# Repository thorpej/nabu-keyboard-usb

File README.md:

# A NABU Keyboard-to-USB Adapter

(Update: I made a short video about this project!  You can view it
[here](https://youtu.be/F3Tp9NLZv1M).)

This is an adapter that lets you connect a [NABU](https://nabu.ca/) PC
keyboard to any modern computer using USB.  In addition to the keyboard,
it reports the Atari-style joysticks as USB HID gamepads (each as a single
D-pad / hat switch with a single "A" button).

Most of the NABU keys are supported in the obvious way, but it's helpful
to understand how the NABU keyboard works: The keyboard, for the most part,
sends ASCII codes for the keys that are pressed.  It handles CTRL, SHIFT,
and CAPS-LOCK all on its own.  It does not send separate key-down and key-up
events for the standard keys, and it implements key-repeat itself as well.
There are some exceptions, however: the arrow keys (including the **<|||**
and **|||>** keys), **YES**, **NO**, **SYM**, **PAUSE** and **TV/NABU** keys
_do_ send separate key-down and key-up events, and are unaffected by the
normal keyboard modifier keys.  These so-called "special keys" are mapped
to various HID key events as described below.

The physical interface to the NABU keyboard is a DIN-6 connector carrying
a power rail and an RS422 differential transmit line.  The RS422 serial
line runs at 6992 baud, with 8 data bits, 1 stop bit, and no parity.  The
odd-ball bit rate is due to the way the clock is derived; the main clock
frequency in the keyboard is 3.58MHz (the NTSC colorburst frequency), and
the MC6803 microcontroller inside the keyboard internally divides the clock
by 4 to derive its "E" clock.  The firmware in the keyboard then configures
the MC6803's on-board UART to divide E by 128 for the baud clock.
Communication with the keyboard is unidirectional; it is not possible to
send commands to the keyboard.

The keyboard is powered by a nominally-12V-but-actally-9V power supply
provided by the NABU.  The keyboard power comes from the NABU's 12V rail,
but is fed to the keyboard through a large power resistor on the NABU's
mainboard, which drops the voltage to ~9V at the keyboard's steady-state
current draw (documentation says 300mA, but my bench supply tells me
310-320mA).  The keyboard contains an on-board regulator to provide its
own +5V power rail.  In any case, a 9V DC power brick that can supply at
least 500mA should be perfect for the job.  The adapter controls the power
to the NABU using a small power MOSFET connected between the 9V return from
the keyboard and and negative terminal of the power supply.

## How the adapter works

The adapter utilizes the built-in UART and GPIO functionality of the
Raspberry Pi Pico microcontroller.  UART0 is used as the adapter's console
(115200 @ 8N1), UART1 is used to receive data from the keyboard, and one
GPIO pin is used to control the power to the keyboard.  Another GPIO is
sampled at start-up time to enable debug messages; debugging is enabled
when the jumper is installed.

When the adapter starts up, it performs all of the initialization required
and then starts up the second core on the Pico to pull data in from the
keyboard.  This loop running on the second core determines if the data is
for the keyboard or one of the joysticks, and then adds the data byte to
the appropriate input queue.

Meanwhile, the primary core powers up the keyboard and enters its main loop.
This main loop performs 4 basic tasks:
* Blinking the status LED on the Pico to indicate various states of the
  adapter.
* Performing a health check of the keyboard.
* Processing incoming data from the keyboard and generating the appropriate
  USB HID report sequences.
* Calling into the TinyUSB stack to perform device-side USB processing.

### LED task

The LED task is pretty simple and just provides a simple way of reporting
the current status of the adapter at-a-glance.  There are 4 blinking sequences:
* Fast blinking to indicate the adapter is waiting for the host to establish
  a USB session.
* Medium blinking to indicate the adapter is connected to the host but waiting
  for the keyboard to show signs of life.
* A heatbeat pattern to indicate everything is operating normally.
* A slow blinking to indicate the adapter has been suspended and the keyboard
  powered off.

### Keyboard health check task

The health check task (a.k.a. "deadcheck") checks to make sure that we've
heard from the keyboard within the last 5 seconds.  When idle, the keyboard
sends a "ping" approximately every 3.7 seconds.  Whenever the keyboard reader
running on the second core receives a byte of data from the keyboard, it
updates a timestamp, which is checked in deadcheck routine.  If the keyboard
fails to check in for two deadcheck intervals, the adapter reboots the
keyboard by cycling power.

### Data processing task

The data processing task (called _hid_task()_ in the code) pulls data
enqueued by the keyboard reader thread and performs the processing necessary
to generate USB HID report sequences.  In addition to regular keystrokes,
error messages from the keyboard and joystick data are also processed here,
as is remote-host-wakeup if the host system is suspended.

Error processing is actually performed all the time, because the periodic
ping from the keyboard comes in as an error message, as does the notification
of a successful power-on-reset.  Additionally, there are internal hardware
errors (bad RAM / ROM, etc.) as well as user errors (too many keys pressed)
that are reported.  Hardware errors result in rebooting the keyboard by
cycling power.

Because the NABU keyboard generates only a single byte for most key presses,
this task has to generate HID report sequences to correctly report the key.
For example, if we get "A" from the keyboard, we have to generate a sequence
of 4 HID reports: _SHIFT_, _SHIFT_ + _A_, _SHIFT_, _(none)_.  These sequences
are encoded in a table indexed by NABU keyboard code.  All of the regular
keys end with a _(none)_ report.

The special keys are a little different.  They send individual key-down and
key-up events to the adapter, so we are able to simply mirror that behavior
to the host.  Additionally, two of the special keys have been mapped to key
modifiers: **SYM** is mapped to **Meta** (a.k.a. Windows, Command, or GUI).
and the **TV/NABU** key is mapped to **Alt** (a.k.a. Option on Macs).  The
adapter tracks the state of those keys and includes them as modifiers in
keyboard HID reports.

Much to the chargin of Unix users worldwide, the NABU keyboard lacks a
backslash key.  On US keyboards, this key is also used for the "pipe"
character (SHIFT + backslash).  We steal the **YES** and **NO** keys on
the NABU keyboard for these characters: **YES** for pipe, **NO** for
backslash (we have to use two different special keys since special keys
are not affected by the SHIFT keys).  Luckily, because we're using a
special key for **Alt**, we can still type guillemets on a Mac by using
**TV/NABU** plus the **YES** and **NO** keys.  _«Absolument merveilleux !»,
a-t-il déclaré._

Ok! To summarize the special keys:
* **Up**, **Down**, **Left**, and **Right** arrow keys map to their regular
  US keyboard equivalents.
* **<|||** maps to **Page Up** and **|||>** maps to **Page Down** (very
  useful for scrolling in Terminal on macOS).
* **SYM** maps to **Meta**, a.k.a. **Windows**, **Command**, **GUI**,
  **⌘**, etc.
* **TV/NABU** maps to **Alt**, a.k.a. **Option**, **⌥**, etc.
* **NO** maps to **\\**, a.k.a. backslash.
* **YES** maps to **|**, a.k.a. pipe, vertical bar, etc. 

### TinyUSB device task

This is just a call into the TinyUSB library that performs device-side
processing.  From here, various callbacks back into the main adapter code
can be made to fetch descriptors, reports, and set suspend/resume state.

## The hardware

The hardware is very simple and is centered around the Raspberry Pi Pico
microcontroller board, wich provides a UART for the debug console, a UART
for the keyboard interface, the USB interface to the host, and general-
purpose I/O facilities for configuration of the adapter and control of the
keyboard's power supply.

Note that the adapter board has 3 separate power rails: +5V (supplied by
the USB host), +3V3 (from the Pico's on-board regulator), and +9V (from an
external DC power brick, for the keyboard).

### Keyboard input

The keyboard uses RS422 differential signalling, so a SN75176A differential
bus transciever is used to convert the keyboard signalling to a TTL-compatible
signal.  The transient suppression circuitry mimics that present in the NABU
PC.

The output of the SN75176A is at 5V TTL logic levels, but the Pico's I/O
interface operates at 3V3 CMOS logic levels, so a level shifter must be
used.  I just picked the 74LVC245 bus transciever for the job because I
had plenty of them handy, even though it's slight overkill.

The 74LVC245's output is connected to the Rx pin of UART1 on the Pico.
That's pretty much it for the keyboard input.

### Keyboard power supply / control

The board has a 5.5mm x 2.1mm center-positive barrel jack for power input
from an external 9V power brick.  There is a diode in-series with the
positive terminal as reverse-polarity protection.  The positive terminal
from this supply goes stright to the keyboard.  The power return line
from the keyboard is attached to the drain of an IRLU110PBF power MOSFET,
and the MOSFET's source is then connected to the negative terminal of the
supply, which is also connected to the board's ground plane.  The gate is
normally pulled down, but can be driven high by a pin on the Pico to complete
the circuit and power on the keyboard.  The IRLU110PBF was selected for its
current rating, relatively low as far as power MOSFETs go (1V) Vgs threshold,
and < 1 Ohm Rds-ON.  There's nothing particularly special about it otherwise,
and this application isn't especially demanding, so feel free to substitute
your favorite MOSFET (so long as it is in a TO-251-3 package and has a GDS
pin configuration).

### Pin headers

There are 2 pin headers on the board:
* J1 provides access to UART0 on the Pico, so you can see informational or
  debug messages that are logged by the firmware running on the Pico.
* JP1, when connected, enables those fairly verbose debugging messages.  The
  pin is sampled when the adapter starts up, so enabling them requires
  unplugging the adapter from USB and plugging it back in after connecting
  the jumper.

### The board layout

I am definitely an amateur when it comes to PCB design and layout, but I did
try to keep the board fairly small while still making it easy to assemble
(all through-hole parts except for the tab on the power MOSFET which you don't
even _really_ have to solder if that's your preference).  The footprints for
the decoupling caps and suppression caps are fairly forgiving, so if you have
1nF and 100nF caps in your parts bin that fit the footprint, by all means use
them.

You will need to put downward-facing pin headers onto your Pico and install
female pin header stand-offs onto the board.  This is because I squeezed the
power MOSFET and its pulldown resistor under the Pico.  This isn't really
much of a compromise in height since there's a big ol' DIN-6 socket at the
back of the board anyhow.  (The board size is largely dictated by the external
connections.)

Space for sockets for the DIP ICs is provided because I like to use them.
Feel free to elide if that's what floats your boat.

There are a couple of "special" parts on the board:
* The resistors used on the board are fairly small for through-hole resistors,
  selected to reduce space requirements.  Happily, they're readily available
  from Mouser.
* The DIN-6 socket is harder to get than it should be (plenty of panel-mount
  flavors, but not PCB-mount, sigh).  The one I selected was the CLIFF
  FC680806, available from Newark / element14 / Farnell.  The Hirschmann
  930 778-200 may also work, and there's a
  [no-name version on Amazon](https://www.amazon.com/dp/B015IGPKPK)
  that looks like a copy of the CLIFF part.

I expect to make small tweaks to the board over time, but mainly just to get
alignment of various externally-facing parts Just Right(tm) in the event that
some enterprising individual wants to make a 3D-printed enclosure for it
(**_hey, if you want to do this, please get in contact with me!_**).

In addition to the KiCad design files, a PDF version of the schematic and
board images are also provided, along with the Gerber files needed to have
the board made by your favorite PCB fabrication house.

### So what do I need to build one of these things?

Most of the parts required are bog-standard, available from lots of places.
The Raspberry Pi Pico, the DIP sockets, and the male and female pin headers
can all be acquired from Amazon.  If you want nice machined DIP sockets
instead of the cheap stamped kind, you can get those from
[Phoenix Enterprises](https://www.peconnectors.com/sockets-dip-ic-machined/),
but they have a minimum order.  The ceramic capacitors are basic parts,
but I've provided links to specific parts that I know will fit the board
footprints.  I've done the same with the resistors.

* 1 - Raspberry Pi Pico
* 2 - 20x1 2.54mm pin header (for the Pico)
* 1 - 2x1 2.54mm pin header (optional) (for debug jumper)
* 1 - 3x1 2.54mm pin header (optional) (for debug console)
* 2 - 20x1 2.54mm female pin header (to receive the Pico - _cannot be
  low-profile - space beneath the Pico is required_)
* 1 - DIP-20 socket (optional)
* 1 - DIP-8 socket (optional)
* 1 - [SN74LVC245](https://www.mouser.com/ProductDetail/595-SN74LVC245ANE4)
  in DIP-20 package
* 1 - [SN75176A](https://www.mouser.com/ProductDetail/595-SN75176AP) in
  DIP-8 package
* 1 - [IRLU110PBF](https://www.mouser.com/ProductDetail/844-IRLU110PBF) or
  equivalent power MOSFET in TO-251-3 package with GDS pin configuration
* 2 - [100nF / 0.1µF ceramic capacitor](https://www.mouser.com/ProductDetail/581-SR215E104MAR)
* 2 - [1nF / 1000pF ceramic capacitor](https://www.mouser.com/ProductDetail/581-SR215A102JARTR1)
* 1 - [180 Ohm resistor](https://www.mouser.com/ProductDetail/603-MFR50SFTE52-180R) that fits in a DIN0207 vertical footprint.
* 1 - [10K Ohm resistor](https://www.mouser.com/ProductDetail/603-MFR50SFTE52-10K) that fits in a DIN0207 horizontal footprint.
* 1 - 1N4001 diode in the standard package.  You can actually use whatever diode floats your boat here (it's not involved in
  any switching, merely used for reverse polarity protection), so long as it has > 18V reverse voltage rating and a 500mA current
  rating.
* 1 - [PCB-mount 5.5mm x 2.1mm DC barrel jack](https://www.mouser.com/ProductDetail/163-179PH-EX)
* 1 - [PCB-mount DIN-6 jack, CLIFF FC680806 or equivalent](https://www.newark.com/cliff-electronic-components/fc680806/din-audio-video-conn-jack-6pos/dp/99AC9154).  Also available [here!](https://www.tme.com/us/en-us/details/fc680806/din-connectors/cliff/d6-fc680806/)
* 1 - [9V @ 500mA-or-better DC power brick with 5.5mm x 2.1mm barrel connector](https://www.mouser.com/ProductDetail/490-SWI12-9-N-P5)
* 1 - Micro-USB cable for connecting the adapter to your computer.

### Assembling the board

You might have your own favorite way of putting these things together.  If
so, hey, you do you!  But for those of you who don't, let me recommend a
few basic pointers that will help making the going a little easier.  I'm
going to assume that you already know the basics of soldering.

First, it's best to assemble the lowest-profile components first, increasing
the height of the board as you go along.  With that in mind, here is the
order I would recommend:

1. R1 and Q1 (the parts that sit beneath the Pico)
2. D1
3. U1 and U3 (or their sockets)
4. C1, C2, C3, and C4
5. R2 (the vertically-mounted resistor next to C3 and C4)
6. Female pin heders for U2 (the Pico)
7. J1 and JP1 (the male pin headers)
8. J3 (the DC barrel jack)
9. J2 (the DIN-6 jack)

If you already installed the pin headers into your Pico, or bought the Pico
with the pin headers pre-installed (hopefully with the long end of the pins
facing downwards), then cool!  Otherwise, a trick that makes it easy is to
place the pin headers into the Pico (with the plastic holder on the bottom
of the Pico and the short end of the pins poking through the Pico board) and
then press that as a unit into the female headers installed on the adapter
board.  That will hold everything steady while you solder the pin headers
to the Pico itself.

### Programming the Pico with the NABU Keyboard to USB firmware

Ok, so you've built the board, now you need to get the firmware onto the Pico.
This is easy!  There's a small button on the Pico board.  What you need to do
is to hold that button down while you connect the Pico to your computer using
the USB cable.  When you do that, the Pico will appear on your computer as a
hard drive with a FAT file system on it named "RPI-RP2" (exactly how this
appears on your computer is left as an exercise to the reader).  All you need
to do is copy the provided **_nabu_keyboard_usb.uf2_** file onto that file
system _et voilà!_ your Pico is programmed and has now attached itself as a
USB HID device with 1 keyboard interface and 2 game pad interfaces!

Once you've programmed the Pico, you're all set.  At this point, I recommend
unplugging it from the computer before attaching the 9V power brick and NABU
keyboard.  Once everything is cabled up, plug the Pico back into your computer
and enjoy typing on those sweet, sweet ALPS key switches!

I hope you have fun with your NABU and I hope you enjoy this silly little
project of mine!  If you end up playing with it, I'd love to hear from you!
You can find me on [Mastodon](https://mastodon.sdf.org/@thorpej)
and on [Twitter](https://twitter.com/thorpej) (for as long as it lasts,
anyway).

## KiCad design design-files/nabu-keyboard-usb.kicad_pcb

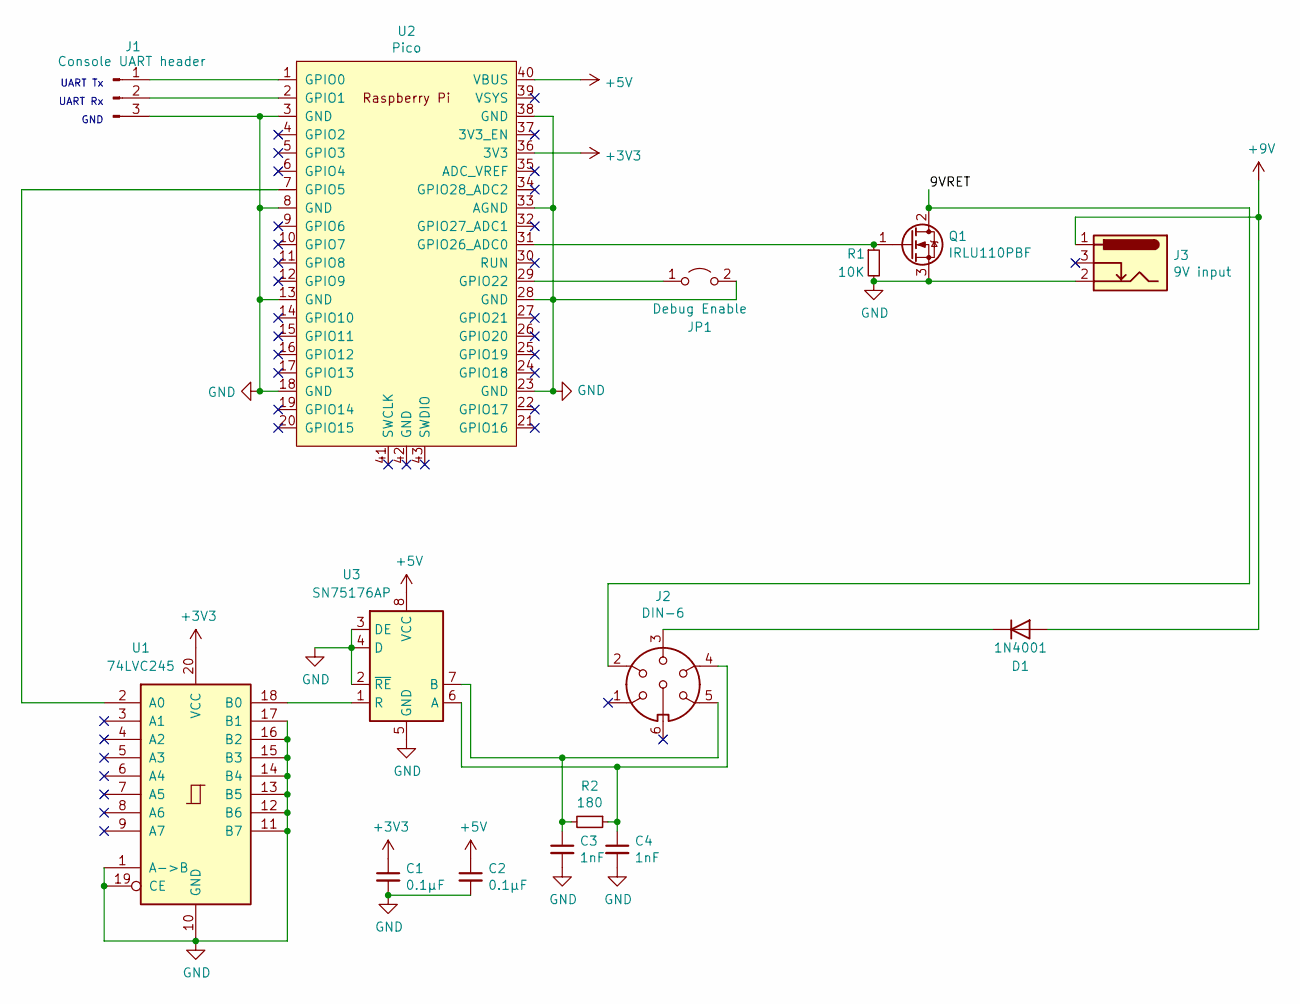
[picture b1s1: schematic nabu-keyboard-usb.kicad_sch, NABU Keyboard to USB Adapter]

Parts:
C1, C2: 0.1µF; C_Disc_D6.0mm_W4.4mm_P5.00mm
C3, C4: 1nF; C_Disc_D6.0mm_W4.4mm_P5.00mm
D1: 1N4001; D_DO-41_SOD81_P10.16mm_Horizontal
J1: Console UART header; PinHeader_1x03_P2.54mm_Vertical
J2: DIN-6; Jack_DIN-6_CLIFF_FC680806
J3: 9V input; Kobiconn_163-179PH-EX-5_5-2_1mm-1_5A
JP1: Debug Enable; PinHeader_1x02_P2.54mm_Vertical
Q1: IRLU110PBF; TO-251-3-1EP_Horizontal_TabDown
R1: 10K; R_Axial_DIN0207_L6.3mm_D2.5mm_P7.62mm_Horizontal; Part YAGEO MFR50SFTE52-10K
R2: 180; R_Axial_DIN0207_L6.3mm_D2.5mm_P2.54mm_Vertical; Part YAGEO MFR50SFTE52-180R
U1: 74LVC245; DIP-20_W7.62mm_Socket
U2: Pico; RPi_Pico_TH
U3: SN75176AP; DIP-8_W7.62mm_Socket

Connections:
+3V3: C1.1, U1.20 (VCC), U2.36 (3V3)
+5V: C2.1, U2.40 (VBUS), U3.8 (VCC)
+9V: D1.2 (A), J3.1
/9VRET: J2.2, Q1.2 (D)
GND: C1.2, C2.2, C3.2, C4.2, J1.3, J3.2, JP1.2 (B), Q1.3 (S), R1.2, U1.1 (A->B), U1.10 (GND), U1.11 (B7), U1.12 (B6), U1.13 (B5), U1.14 (B4), U1.15 (B3), U1.16 (B2), U1.17 (B1), U1.19 (CE), U2.3 (GND), U2.8 (GND), U2.13 (GND), U2.18 (GND), U2.23 (GND), U2.28 (GND), U2.33 (AGND), U2.38 (GND), U3.2 (~RE), U3.3 (DE), U3.4 (D), U3.5 (GND)
unnamed: D1.1 (K), J2.3
unnamed: J1.1, U2.1 (GPIO0)
unnamed: J1.2, U2.2 (GPIO1)
unnamed: JP1.1 (A), U2.29 (GPIO22)
unnamed: Q1.1 (G), R1.1, U2.31 (GPIO26_ADC0)
unnamed: U1.2 (A0), U2.7 (GPIO5)
unnamed: U1.18 (B0), U3.1 (R)
unnamed: C4.1, J2.4, R2.1, U3.6 (A)
unnamed: C3.1, J2.5, R2.2, U3.7 (B)

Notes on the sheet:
GND
UART Tx
UART Rx

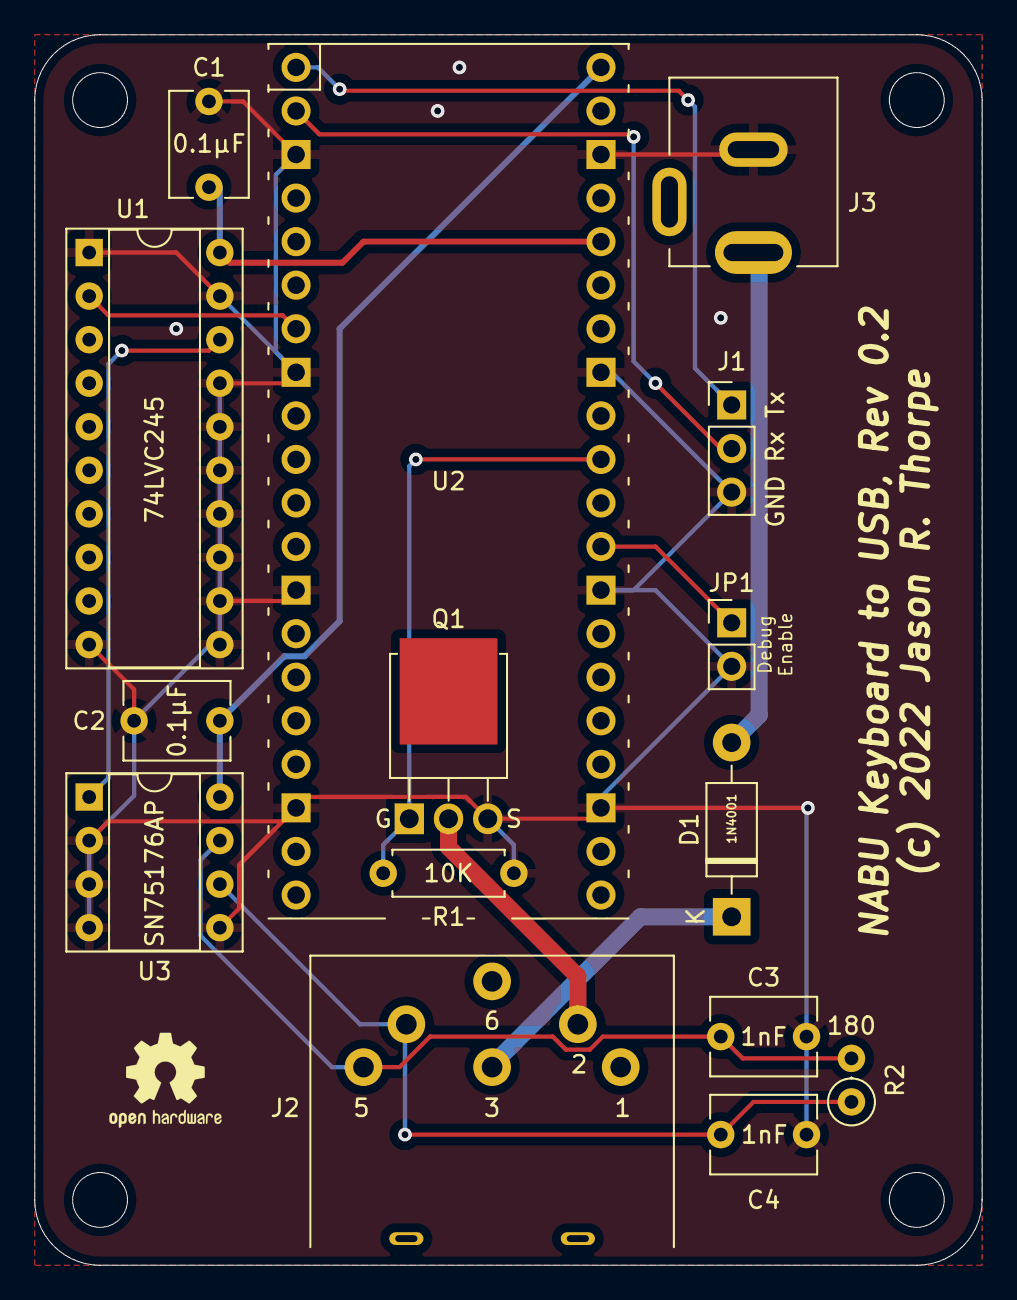
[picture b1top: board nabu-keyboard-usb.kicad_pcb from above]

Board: 2 copper layers, 55.2 x 71.8 mm, 15 parts (0 on the bottom side), 14 nets.

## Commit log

2022-12-07 Add USB HID keycodes from:
    https://gist.github.com/MightyPork/6da26e382a7ad91b5496ee55fdc73db2
2022-12-07 Add KEY_ERR_POST and KEY_ERR_UNDEF; the NABU keyboard can report these.
2022-12-10 Checkpoint W-I-P.
2022-12-10 Checkpoint W.I.P. -- compiles now.
2022-12-10 Checkpoint: Builds with USB headers now.
2022-12-10 Checkpoint: LED should blink now.
2022-12-12 Checkpoint: Can send simulated keystrokes (that go through the NABU mapping table).
2022-12-12 Fix a silly bug in the keystroke stimulator that resulted in extra unintended keystrokes.
2022-12-12 Fix key event reporting to correctly use the Report protocol. Modifier keys now work on NetBSD.
2022-12-12 Properly deal with M_DOWN / M_UP keys, and tidy up debug messages.
2022-12-12 Checkpoint: Error / heartbeat messages from keyboard.
2022-12-12 Sample GP22 when we start up -- it's pulled up to Vdd, but if tied to GND we enable debug messages.
2022-12-12 Use GP26 to control the power of the NABU keyboard.
2022-12-12 Fix dumb bug in kbd_getc()'s simulation case.
2022-12-12 Fix error spew when deadcheck fails.
2022-12-12 Enable the gamepad report descriptors.
2022-12-13 First pass at using SYM as a META/GUI (Windows / Cloverleaf) bucky bit.
2022-12-13 Fix the HID report descroptor for joystick 1.
2022-12-13 Allow GP14 and GP15 to trigger simulated Cmd-c / Cmd-v sequences when touched to GND. Verified SYM -> META logic works as expected.
2022-12-13 Remove some rendundant declarations.
2022-12-13 Track whether we've seen the keyboard's RESET message. When we know we've powered off the keyboard, set have_nabu to false. This causes the deadcheck to politely state that it's waiting for the keybo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
2022-12-13 Drain the keyboard of any junk before launching the reader thread on Core 1, and wait for Core 1 to be ready before powering up the keyboard for the first time.
2022-12-13 Bump the simulator's initial delay to 6 seconds so we can see the "Waiting for..." message from the deadcheck.
2022-12-13 Clean up some comments around debug_printf().
2022-12-13 Fix a comment.
2022-12-13 Put the logic for "device has data" into keyboard and joystick-specific functions.
2022-12-13 Pass the current timestamp to the task functions rather than computing it each time.
2022-12-13 Call kbd_deadcheck() from the main loop, not hid_task().
2022-12-14 Cange pins used for Cmd-c / Cmd-v injection to make the PCB layout a bit better.
2022-12-14 First crack at schematic / PCB. Don't have footprint information for the DIN-6 connector yet, so there's a placeholder instead.
2022-12-14 Correct name in comment block.
2022-12-17 Disable the keystroke simulation stuff. Code is working against a real NABU keyboard.
2022-12-17 Oops, UP and DOWN arrows were swapped. I blame the manual.
2022-12-17 Map the TV/NABU key to Alt. It's kind of the last "good" choice left. I can see the argument, tho, for swapping Alt and GUI, so perhaps I'll make that configurable via jumper.
2022-12-17 Improve debug logging for joystick codes.
2022-12-17 Ok, we're 0.2 at this point, since things are basically working.
2022-12-18 Bump some timeout values.
2022-12-18 Fix sending META and ALT modifiers.
2022-12-18 Take over YES and NO keys to use for | and \, respectively. Bump version to 0.4.
2022-12-19 Improve status LED patterns.
2022-12-19 Suspend / resume now works (at least against macOS).
2022-12-19 De-glitch the RS422 input in the same fashion as the NABU.
2022-12-19 We have a mapping for Alt / Opt now... delete the TODO item.
2022-12-19 G/C the SIMULATE_KEYSTROKES stuff. It was super useful when bringing up the board, but it's no longer needed.
2022-12-19 Update README.md
    First crack at the README that describes how the adapter works.
2022-12-19 Oops, mmissed some SIMULATE_KEYSTROKES bits when it was G/C'd.
2022-12-19 Add build and uf2 product directories.
2022-12-20 Update README.md
    Info about the hardware.
2022-12-20 Update README.md
    More hardware description + BoM.
2022-12-20 Update README.md
    Clarify footprint arrangement for the resistors.
2022-12-20 Update README.md
    Fix a typo.
2022-12-21 Enable some additional compiler warnings.
2022-12-21 Add timestamps to non-DEBUG messages. Bump version to 0.5
2022-12-21 Finalize the first prototype PCB.
2022-12-21 Fix a couple of minor schematic errors.
2022-12-21 Add UF2 file of the current firmware.
2022-12-24 Found another place to get the CLIFF DIN-6 jack!
2022-12-24 Link to the DIN-6 jack on Amazon that I found. It appears to be a very close copy of the CLIFF part.
2023-04-07 nabu-usb-keyboard --> nabu-keyboard-usb
2023-04-09 Convert to KiCad 6 format.
2023-04-09 Remove KiCad 5 files.
2023-04-09 Fix an error in the schematic that resulted in a non-working PCB; TX+ and TX- were swapped going into the 75176.
2023-04-10 Update PCB silkscreen to reflect rev bump and make new font/back images.
2023-04-10 Regenerate Gerbers for rev 0.2 PCB.
2023-04-10 Update README.md
    Remove any discussion of 12V supply -- 9V is what we want. Document the polarity protection diode.
2023-04-13 Update README.md
    Fix a couple of typos.
2023-05-21 Re-flow text for 80 columns. Add link to video about the project.
2023-05-21 Fix a markup botch.
2023-05-21 Fix another markup botch.

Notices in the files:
design-files/nabu-keyboard-usb.kicad_pcb:
(c) 2022 Jason R. Thorpe. See LICENSE.
